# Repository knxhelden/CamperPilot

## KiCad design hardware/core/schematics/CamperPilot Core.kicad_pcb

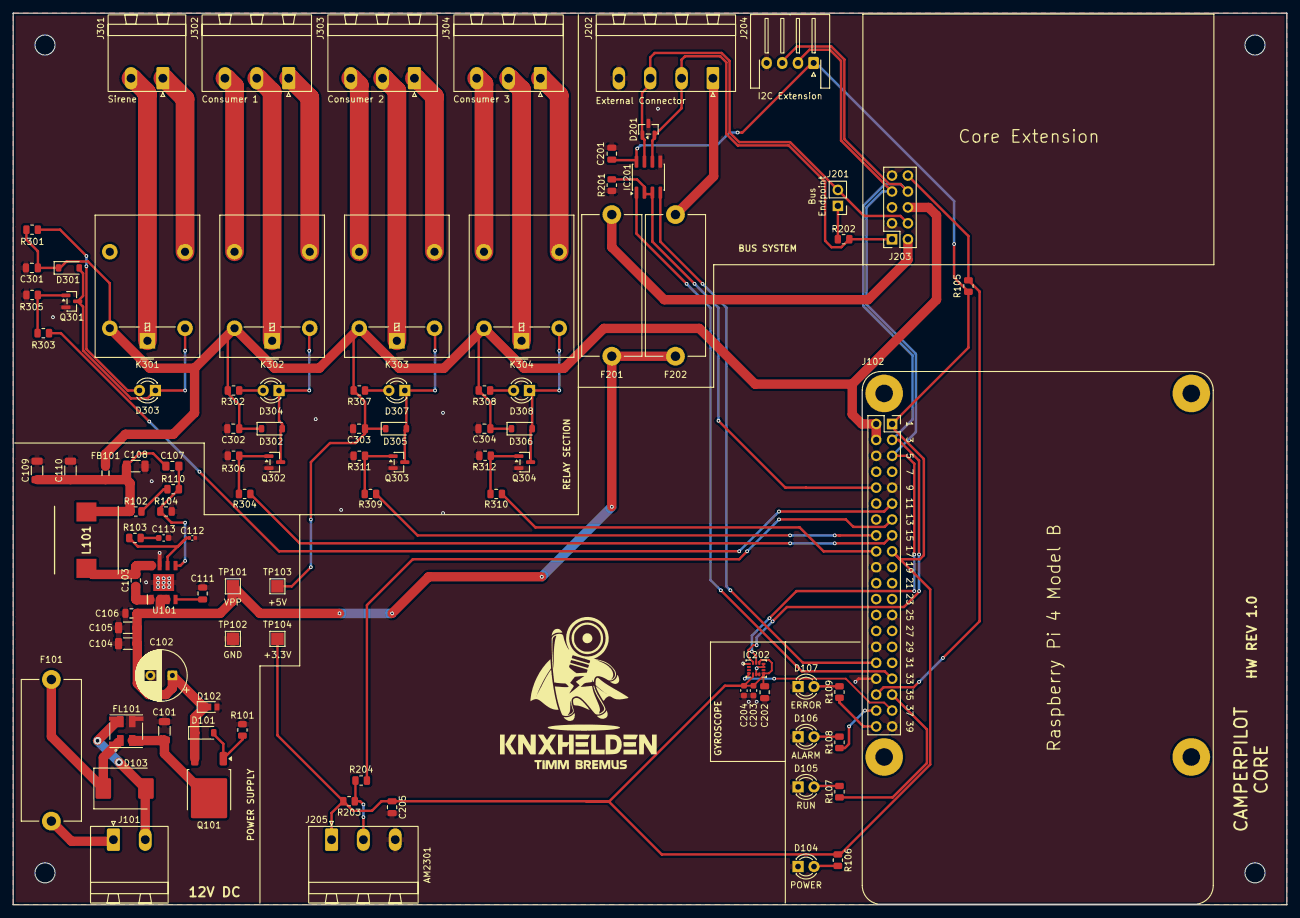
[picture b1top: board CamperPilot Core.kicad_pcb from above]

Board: 4 copper layers, 203.2 x 142.2 mm, 101 parts (0 on the bottom side), 65 nets.

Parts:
C101, C104, C105: 10µF/50V; C_1206_3216Metric
C102: 100µF; CP_Radial_D8.0mm_P3.50mm
C103, C106, C201, C202, C205: 100nF; C_0805_2012Metric
C107: C; C_0805_2012Metric_Pad1.18x1.45mm_HandSolder
C108, C109, C110: 22µF; C_1206_3216Metric
C111: 10nF; C_0805_2012Metric
C112: 33pF; C_0402_1005Metric
C113: 2.7nF; C_0603_1608Metric
C203: 2.2uF; C_0603_1608Metric
C204: 10nF; C_0603_1608Metric
C301, C302, C303, C304: 1µF; C_0805_2012Metric
D101: BZT52C12; D_SOD-123
D102: CUHZ30V,H3F; D_Toshiba_US2H_CUHZ30V
D103: TPSMC18CA-VR; D_SMC
D104: POWER; LED_D3.0mm
D105: RUN; LED_D3.0mm
D106: ALARM; LED_D3.0mm
D107: ERROR; LED_D3.0mm
D201: CDSOT23-SM712; SOT-23
D301, D302, D305, D306: 1N4148W; D_SOD-123
D303, D304, D307, D308: Green LED; LED_D3.0mm
F101: 3A; Fuseholder_Cylinder-5x20mm_Stelvio-Kontek_PTF78_Horizontal_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
F201, F202: 500mA; Fuseholder_Cylinder-5x20mm_Stelvio-Kontek_PTF78_Horizontal_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
FB101: MPZ2012S300AT000; L_0805_2012Metric
FL101: DLW5BTM501SQ2L; L_CommonModeChoke_Murata_DLW5BTMxxxSQ2x_5x5mm
H101, H102, H103, H104: M3; MountingHole_3.2mm_M3
IC201: THVD1410DR; SOIC-8_3.9x4.9mm_P1.27mm
IC202: ICM-42670-P; LGA-14_3x2.5mm_P0.5mm_LayoutBorder3x4y
J101: Battery; PhoenixContact_MSTBA_2,5_2-G-5,08_1x02_P5.08mm_Horizontal
J102: Raspberry Pi 4 Model B; Raspberry Pi 4
J201: Endpoint Jumper; PinHeader_1x02_P2.54mm_Vertical
J202: External Connector; PhoenixContact_MSTBA_2,5_4-G_1x04_P5.00mm_Horizontal
J203: Internal Connector; PinSocket_2x05_P2.54mm_Vertical
J204: I2C Extension; JST_XH_S4B-XH-A-1_1x04_P2.50mm_Horizontal
J205: AM2301; PhoenixContact_MSTBA_2,5_3-G-5,08_1x03_P5.08mm_Horizontal
J301: Sirene; PhoenixContact_MSTBA_2,5_2-G-5,08_1x02_P5.08mm_Horizontal
J302: Consumer 1; PhoenixContact_MSTBA_2,5_3-G-5,08_1x03_P5.08mm_Horizontal
J303: Consumer 2; PhoenixContact_MSTBA_2,5_3-G-5,08_1x03_P5.08mm_Horizontal
J304: Consumer 3; PhoenixContact_MSTBA_2,5_3-G-5,08_1x03_P5.08mm_Horizontal
K301, K302, K303, K304: G5LE-14-DC5; Relay_SPDT_Omron-G5LE-1
L101: 4,7µH; INDPM108102X400N
Q101: DMP4051LK3Q-13; TO-252-2
Q301, Q302, Q303, Q304: AO3400A; SOT-23
R101: 2,2kΩ; R_0805_2012Metric
R102: 51k; R_0805_2012Metric
R103: 15kΩ; R_0805_2012Metric
R104, R105, R201, R305, R306, R311, R312: 10kΩ; R_0805_2012Metric
R106, R107, R108, R109, R303, R304, R309, R310: 470Ω; R_0805_2012Metric
R110: 2.7k; R_0805_2012Metric
R202: 120Ω; R_0805_2012Metric
R203: 4,7kΩ; R_0805_2012Metric
R204: 220Ω; R_0805_2012Metric
R301, R302, R307, R308: 1kΩ; R_0805_2012Metric
TP101: VPP; TestPoint_Pad_2.0x2.0mm
TP102: GND; TestPoint_Pad_2.0x2.0mm
TP103: +5V; TestPoint_Pad_2.0x2.0mm
TP104: +3.3V; TestPoint_Pad_2.0x2.0mm
U101: AP64501QSP-13

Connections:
+3.3V: C201.2, C202.1, C203.1, C204.1, C205.1, IC201.8 (VCC), IC202.5 (VDDIO), IC202.8 (VDD), IC202.12 (AP_CS), J102.1 (3V3), J102.17 (3V3), J204.1, J205.1, R105.2, R106.1, R203.1, TP104.1 (1_1)
+5V: C301.1, C302.1, C303.1, C304.1, D301.1 (K), D302.1 (K), D305.1 (K), D306.1 (K), FB101.1, J102.2 (5V), J102.4 (5V), J203.6, K301.5, K302.5, K303.5, K304.5, R301.1, R302.1, R307.1, R308.1, TP103.1 (1_1)
+BAT: D103.1 (A1), F101.2, FL101.1
-BAT: D103.2 (A2), FL101.4, J101.2
/GPIO12: IC201.4 (D), J102.32 (GPIO12/PWM0)
/GPIO13: IC201.1 (R), J102.33 (GPIO13/PWM1)
/GPIO15: IC201.2 (~RE), IC201.3 (DE), J102.10 (GPIO15/UART_RXD), R201.2
/GPIO16: J102.36 (GPIO16/SPI1_~CE2), J203.10, R105.1
/GPIO17: J102.11 (GPIO17/SPI1_~CE1), R303.1
/GPIO19: J102.35 (GPIO19/SPI1_MISO/PCM_FS), R107.1
/GPIO20: J102.38 (GPIO20/SPI1_MOSI/PCM_DIN/PWM1), R108.1
/GPIO21: J102.40 (GPIO21/SPI1_SCLK/PCM_DOUT), R109.1
/GPIO22: J102.15 (GPIO22/SDIO_CLK), R304.1
/GPIO23: J102.16 (GPIO23/SDIO_CMD), R309.1
/GPIO24: J102.18 (GPIO24/SDIO_DAT0), R310.1
/GPIO26: IC202.4 (INT1_/_INT), J102.37 (GPIO26/SDIO_DAT2)
/GPIO27: J102.13 (GPIO27/SDIO_DAT3), R204.1
/Peripherie/RS485_A: D201.2, IC201.6 (A), J202.2, J203.1, R202.2
/Peripherie/RS485_B: D201.1, IC201.7 (B), J201.2, J202.3, J203.4
/SCL: IC202.13 (AP_SCL_/_AP_SCLK), J102.5 (SCL_I2C1/GPIO03), J203.7, J204.2
/SDA: IC202.14 (AP_SDA_/_AP_SDIO_/_AP_SDI), J102.3 (SDA_I2C1/GPIO02), J203.8, J204.3
GND: C101.2, C102.2, C104.2, C105.2, C106.2, C108.2, C109.2, C110.2, C111.2, C112.2, C113.2, C201.1, C202.2, C203.2, C204.2, C205.2, C301.2, C302.2, C303.2, C304.2, D102.2 (A), D104.1 (K), D105.1 (K), D106.1 (K), D107.1 (K), D201.3, FL101.3, IC201.5 (GND), IC202.1 (AP_SDO_/_AP_AD0), IC202.6 (GND), IC202.7 (FSYNC), IC202.10 (RESV_3), IC202.11 (RESV_4), J102.6 (GND), J102.9 (GND), J102.14 (GND), J102.20 (GND), J102.25 (GND), J102.30 (GND), J102.34 (GND), J102.39 (GND), J202.4, J203.3, J203.9, J204.4, J205.3, Q301.2 (S), Q302.2 (S), Q303.2 (S), Q304.2 (S), R101.2, R104.2, R201.1, R305.1, R306.1, R311.1, R312.1, TP102.1 (1_1), U101.7 (GND), U101.9 (EP)
unnamed: C107.1, C108.1, C109.1, C110.1, FB101.2, L101.2, R102.1
unnamed: C113.1, R103.2
unnamed: D101.2 (A), Q101.1 (G), R101.1
unnamed: D104.2 (A), R106.2
unnamed: D105.2 (A), R107.2
unnamed: D106.2 (A), R108.2
unnamed: D107.2 (A), R109.2
unnamed: D301.2 (A), D303.1 (K), K301.2, Q301.3 (D)
unnamed: D302.2 (A), D304.1 (K), K302.2, Q302.3 (D)
unnamed: D303.2 (A), R301.2
unnamed: D304.2 (A), R302.2
unnamed: D305.2 (A), D307.1 (K), K303.2, Q303.3 (D)
unnamed: D306.2 (A), D308.1 (K), K304.2, Q304.3 (D)
unnamed: D307.2 (A), R307.2
unnamed: D308.2 (A), R308.2
unnamed: F101.1, J101.1
unnamed: J201.1, R202.1
unnamed: F202.2, J202.1
unnamed: F201.2, J203.2
unnamed: J205.2, R203.2, R204.2
unnamed: J301.1, K301.3
unnamed: J301.2, K301.1
unnamed: J302.1, K302.3
unnamed: J302.2, K302.1
unnamed: J302.3, K302.4
unnamed: J303.1, K303.3
unnamed: J303.2, K303.1
unnamed: J303.3, K303.4
unnamed: J304.1, K304.3
unnamed: J304.2, K304.1
unnamed: J304.3, K304.4
unnamed: C101.1, FL101.2, Q101.2 (D)
unnamed: Q301.1 (G), R303.2, R305.2
unnamed: Q302.1 (G), R304.2, R306.2
unnamed: Q303.1 (G), R309.2, R311.2
unnamed: Q304.1 (G), R310.2, R312.2
unnamed: R102.2, R110.1
unnamed: C103.1, U101.1 (BST)
unnamed: C112.1, R103.1, U101.6 (COMP)
unnamed: C107.2, R104.1, R110.2, U101.5 (FB)
unnamed: C111.1, U101.4 (SS)
unnamed: C103.2, L101.1, U101.8 (SW)
VPP: C102.1, C104.1, C105.1, C106.1, D101.1 (K), D102.1 (K), F201.1, F202.1, Q101.3 (S), TP101.1 (1_1), U101.2 (VIN), U101.3 (EN)

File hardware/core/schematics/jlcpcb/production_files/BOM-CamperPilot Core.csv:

Comment,Designator,Footprint,LCSC,Quantity
100nF,"C103,C106,C201,C202,C205",C_0805_2012Metric,C49678,5
10kΩ,"R104,R105,R201,R305,R306,R311,R312",R_0805_2012Metric,C17414,7
10nF,C204,C_0603_1608Metric,C57112,1
10µF/50V,"C101,C104,C105",C_1206_3216Metric,C13585,3
1N4148W,"D301,D302,D305,D306",D_SOD-123,C81598,4
1kΩ,"R301,R302,R307,R308",R_0805_2012Metric,C17513,4
1µF,"C301,C302,C303,C304",C_0805_2012Metric,C28323,4
"2,2kΩ",R101,R_0805_2012Metric,C17520,1
2.2uF,C203,C_0603_1608Metric,C23630,1
2.7nF,C113,C_0603_1608Metric,C1609,1
22µF,"C108,C109,C110",C_1206_3216Metric,C12891,3
33pF,C112,C_0402_1005Metric,C1562,1
470Ω,"R106,R107,R108,R109,R303,R304,R309,R310",R_0805_2012Metric,C17710,8
DLW5BTM501SQ2L,FL101,L_CommonModeChoke_Murata_DLW5BTMxxxSQ2x_5x5mm,C91597,1
DMP4051LK3Q-13,Q101,TO-252-2,C6183711,1
TPSMC18CA-VR,D103,D_SMC,C1973213,1
G5LE-14-DC5,K301,Relay_SPDT_Omron-G5LE-1,,1
"4,7kΩ",R203,R_0805_2012Metric,,1
"4,7µH",L101,WE-LHMI_104048,,1
100µF,C102,CP_Radial_D8.0mm_P3.50mm,,1
+3.3V,TP104,TestPoint_Pad_2.0x2.0mm,,1
AO3400A,Q302,SOT-23,,1
"53,6kΩ",R102,R_0805_2012Metric,,1
MPZ2012S300AT000,FB101,L_0805_2012Metric,,1
Green LED,D304,LED_D3.0mm,,1
500mA,F202,Fuseholder_Cylinder-5x20mm_Stelvio-Kontek_PTF78_Horizontal_Open,,1
Consumer 3,J304,"PhoenixContact_MSTBA_2,5_3-G-5,08_1x03_P5.08mm_Horizontal",,1
G5LE-14-DC5,K302,Relay_SPDT_Omron-G5LE-1,,1
500mA,F201,Fuseholder_Cylinder-5x20mm_Stelvio-Kontek_PTF78_Horizontal_Open,,1
ICM-42670-P,IC202,ICM42670P,,1
RUN,D105,LED_D3.0mm,,1
Battery,J101,"PhoenixContact_MSTBA_2,5_2-G-5,08_1x02_P5.08mm_Horizontal",,1
BZT52C12,D101,D_SOD-123F,,1
Sirene,J301,"PhoenixContact_MSTBA_2,5_2-G-5,08_1x02_P5.08mm_Horizontal",,1
I2C Extension,J204,JST_XH_S4B-XH-A-1_1x04_P2.50mm_Horizontal,,1
220Ω,R204,R_0805_2012Metric,,1
Green LED,D307,LED_D3.0mm,,1
+5V,TP103,TestPoint_Pad_2.0x2.0mm,,1
3A,F101,Fuseholder_Cylinder-5x20mm_Stelvio-Kontek_PTF78_Horizontal_Open,,1
VPP,TP101,TestPoint_Pad_2.0x2.0mm,,1
AO3400A,Q304,SOT-23,,1
AM2301,J205,"PhoenixContact_MSTBA_2,5_3-G-5,08_1x03_P5.08mm_Horizontal",,1
AO3400A,Q303,SOT-23,,1
"CUHZ30V,H3F",D102,D_Toshiba_US2H_CUHZ30V,,1
ERROR,D107,LED_D3.0mm,,1
Consumer 2,J303,"PhoenixContact_MSTBA_2,5_3-G-5,08_1x03_P5.08mm_Horizontal",,1
Internal Connector,J203,PinHeader_2x05_P2.54mm_Vertical,,1
G5LE-14-DC5,K304,Relay_SPDT_Omron-G5LE-1,,1
120Ω,R202,R_0805_2012Metric,,1
GND,TP102,TestPoint_Pad_2.0x2.0mm,,1
"15,8kΩ",R103,R_0805_2012Metric,,1
Endpoint Jumper,J201,PinHeader_1x02_P2.54mm_Vertical,,1
AP64501QSP-13,U101,AP64501QSP-13,,1
Consumer 1,J302,"PhoenixContact_MSTBA_2,5_3-G-5,08_1x03_P5.08mm_Horizontal",,1
POWER,D104,LED_D3.0mm,,1
CDSOT23-SM712,D201,SOT95P230X117-3N,,1
ALARM,D106,LED_D3.0mm,,1
AO3400A,Q301,SOT-23,,1
Green LED,D303,LED_D3.0mm,,1
Green LED,D308,LED_D3.0mm,,1
G5LE-14-DC5,K303,Relay_SPDT_Omron-G5LE-1,,1
Raspberry Pi 4 Model B,J102,Raspberry Pi 4,,1
External Connector,J202,"PhoenixContact_MSTBA_2,5_4-G_1x04_P5.00mm_Horizontal",,1
THVD1410DR,IC201,SOIC127P600X175-8N,,1
